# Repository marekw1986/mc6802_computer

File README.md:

# MC6802 computer

Currently this code only consists some I/O routines for MC6802 
based system.

This project is still in development. It's going to be simple BASIC computer.

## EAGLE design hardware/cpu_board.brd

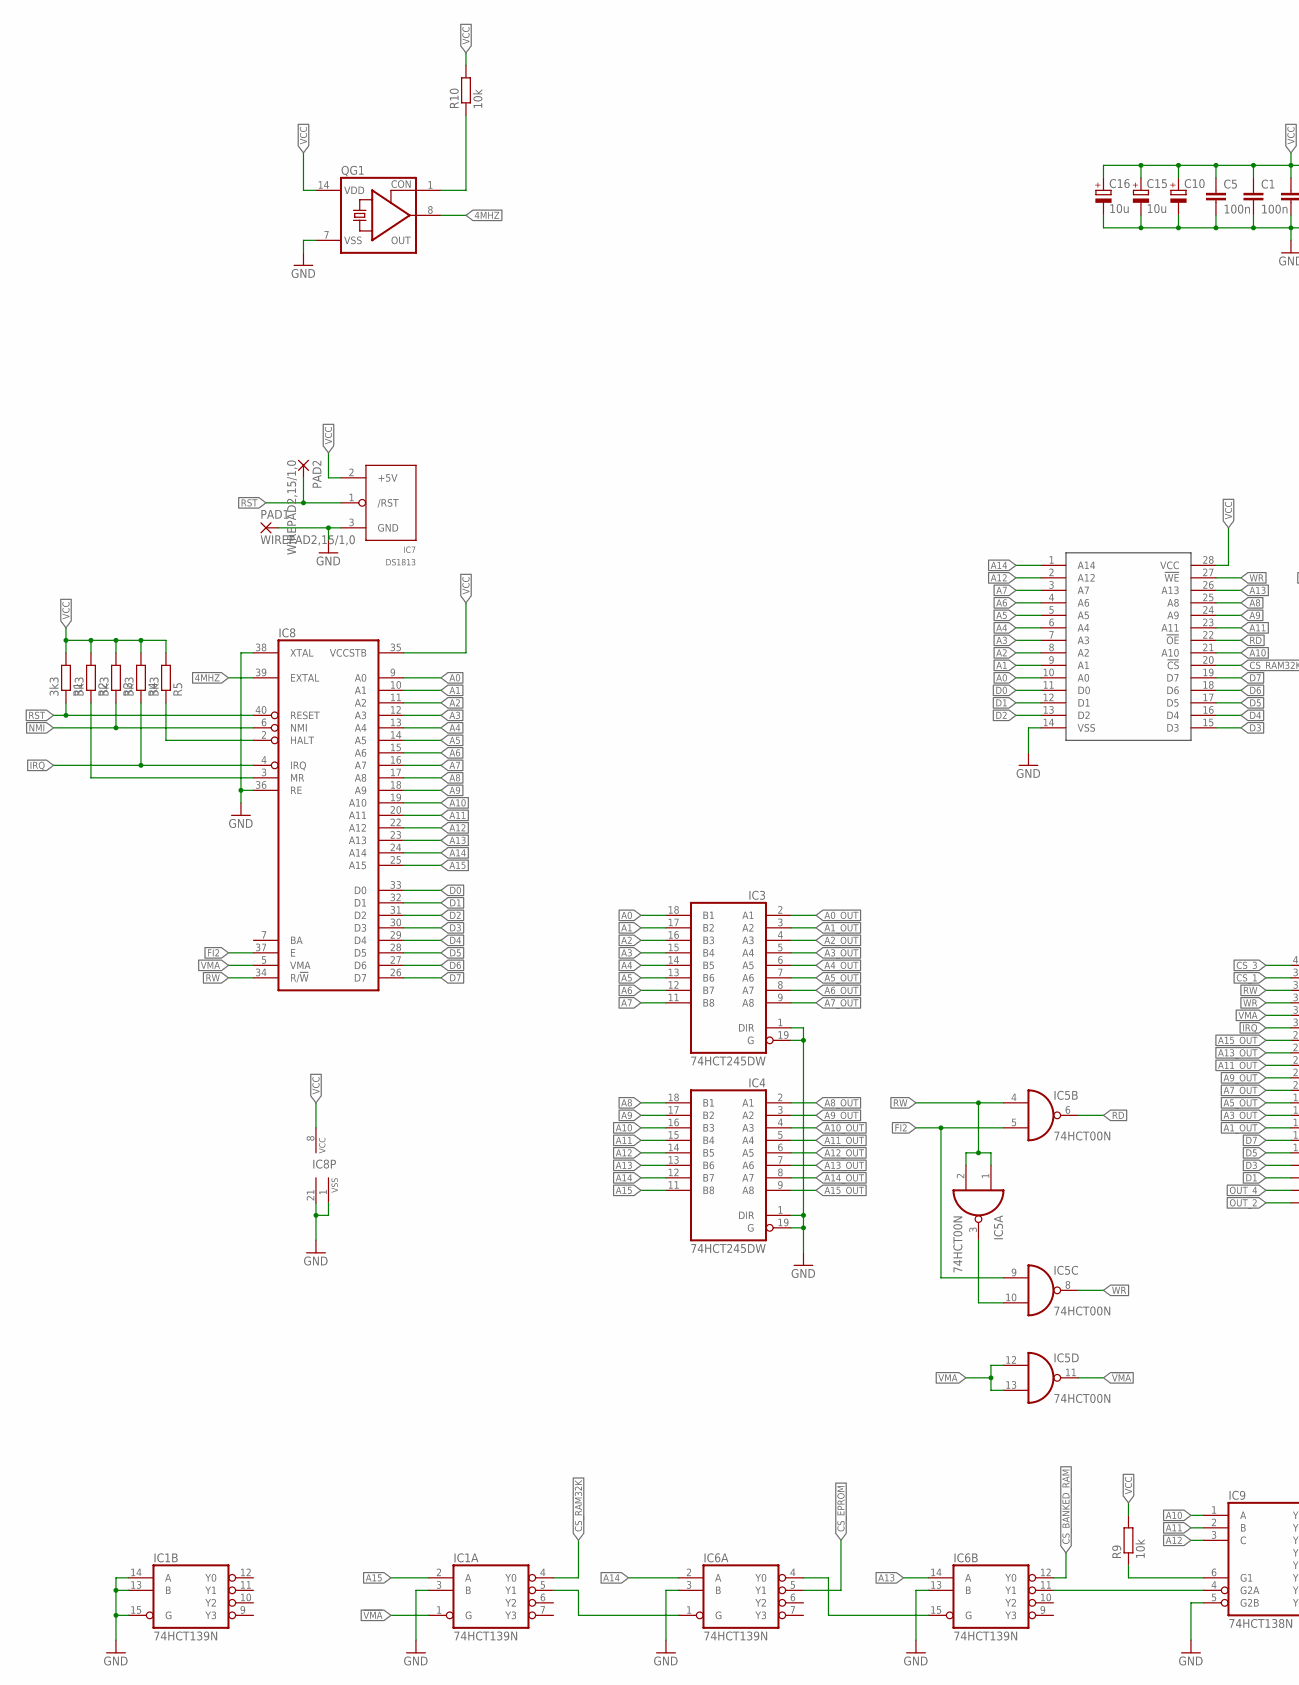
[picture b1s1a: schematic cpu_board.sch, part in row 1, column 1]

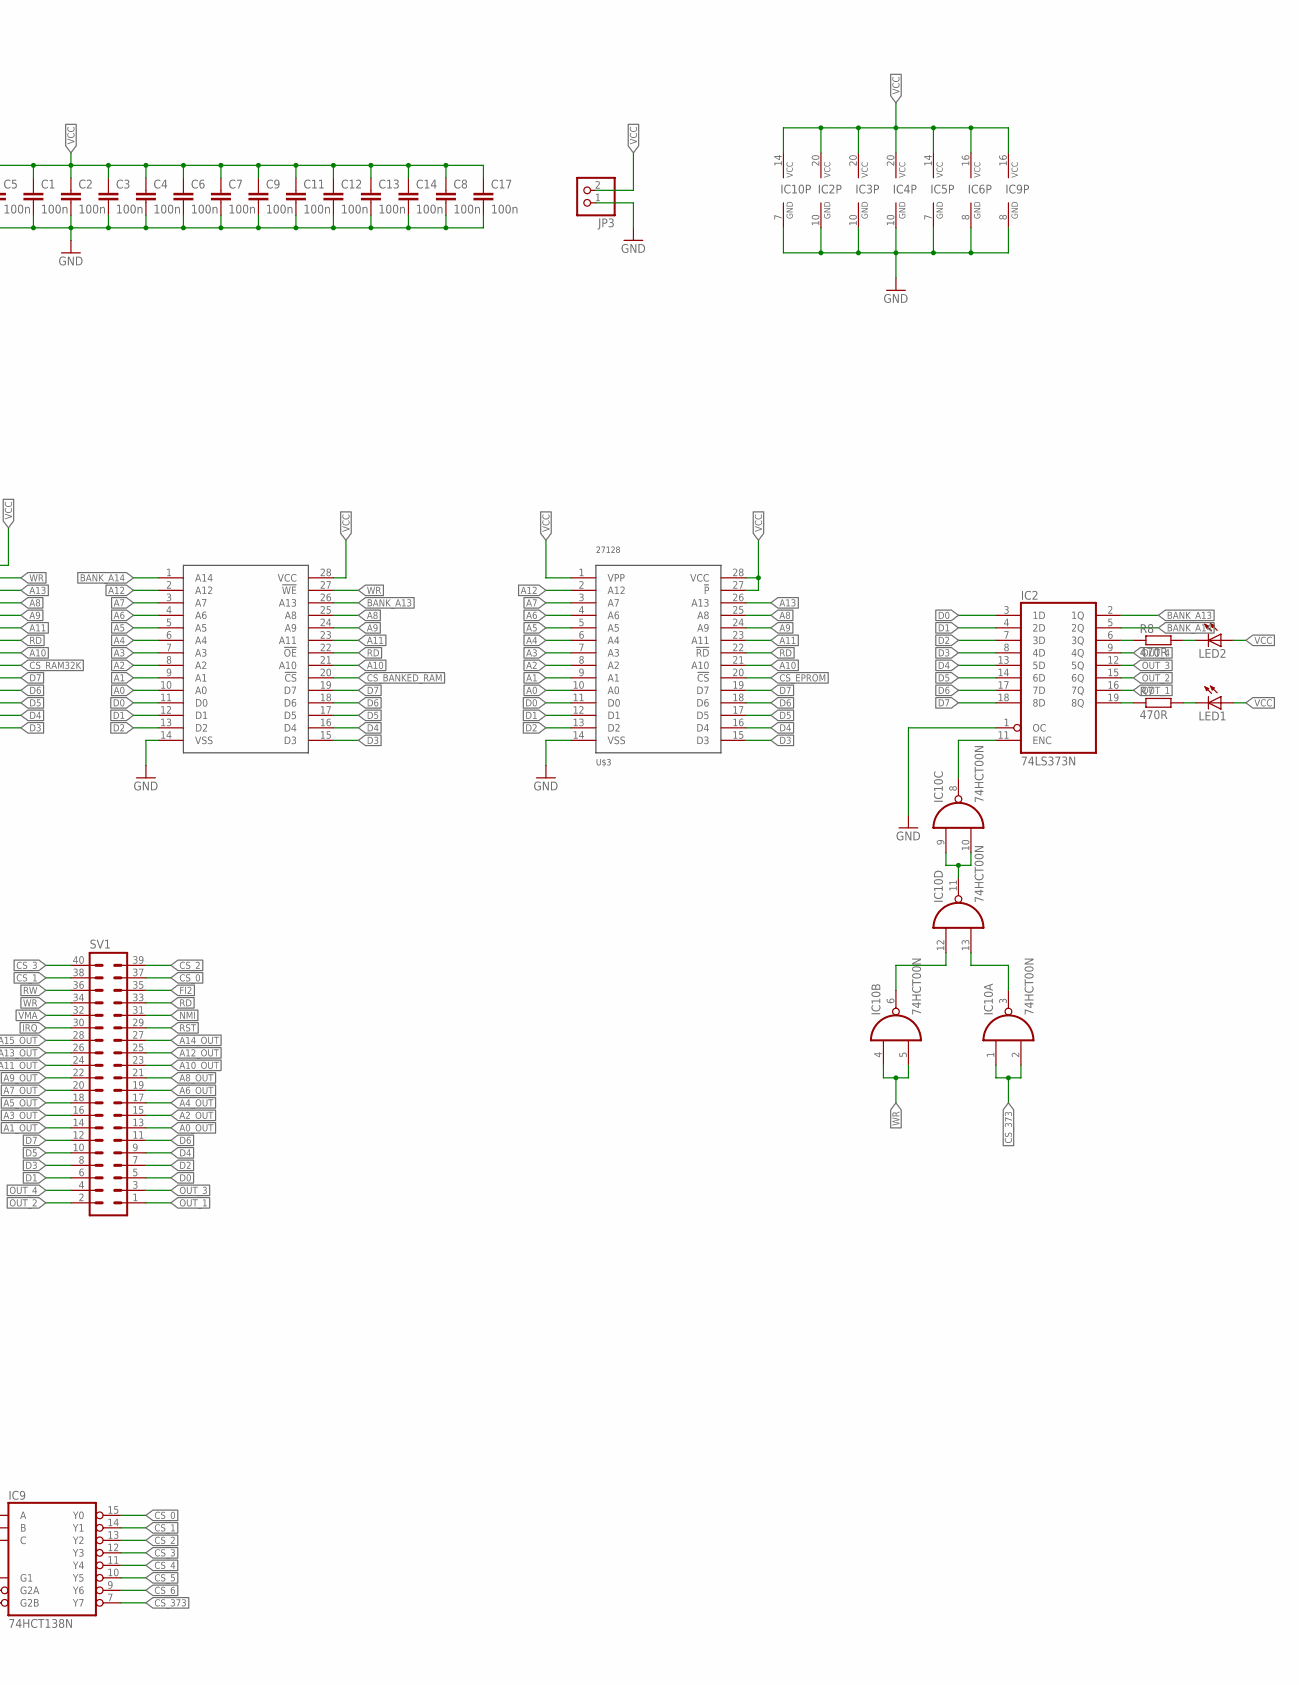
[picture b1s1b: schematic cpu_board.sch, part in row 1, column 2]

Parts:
C1, C2, C3, C4, C6, C8, C9: 100n; C1206
C5, C7, C14: 100n; C0603
C10: CPOL-EUE5-10.5; E5-10,5
C11, C12, C13, C17: 100n; C0805
C15, C16: 10u; SMC_B
IC1, IC6: 74HCT139N; DIL16
IC2: 74LS373N; DIL20
IC3, IC4: 74HCT245DW; SO20W
IC5, IC10: 74HCT00N; DIL14
IC7: DS1813; TO-92
IC8: 6802; DIL40
IC9: 74HCT138N; DIL16
JP3: PINHD-1X2/90; 1X02/90
LED1, LED2: LED5MM
PAD1, PAD2: WIREPAD2,15/1,0; 2,15/1,0
QG1: CRYSTAL_RES-SG51; SG51
R1, R2, R3, R5: 3k3; R1206
R4: 3k3; R0603
R7, R8: 470R; R1206
R9: 10k; 0204/7
R10: 10k; R1206
SV1: ML40L
U$2, U$4: 62256; DIL28-6
U$3: 27128; DIL28

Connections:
4MHZ: IC8.39 (EXTAL), QG1.8 (OUT)
!VMA: IC1.1 (G), IC5.11 (O)
A0: IC3.18 (B1), IC8.9 (A0), U$2.10 (A0), U$3.10 (A0), U$4.10 (A0)
A0_OUT: IC3.2 (A1), SV1.13
A1: IC3.17 (B2), IC8.10 (A1), U$2.9 (A1), U$3.9 (A1), U$4.9 (A1)
A1_OUT: IC3.3 (A2), SV1.14
A2: IC3.16 (B3), IC8.11 (A2), U$2.8 (A2), U$3.8 (A2), U$4.8 (A2)
A2_OUT: IC3.4 (A3), SV1.15
A3: IC3.15 (B4), IC8.12 (A3), U$2.7 (A3), U$3.7 (A3), U$4.7 (A3)
A3_OUT: IC3.5 (A4), SV1.16
A4: IC3.14 (B5), IC8.13 (A4), U$2.6 (A4), U$3.6 (A4), U$4.6 (A4)
A4_OUT: IC3.6 (A5), SV1.17
A5: IC3.13 (B6), IC8.14 (A5), U$2.5 (A5), U$3.5 (A5), U$4.5 (A5)
A5_OUT: IC3.7 (A6), SV1.18
A6: IC3.12 (B7), IC8.15 (A6), U$2.4 (A6), U$3.4 (A6), U$4.4 (A6)
A6_OUT: IC3.8 (A7), SV1.19
A7: IC3.11 (B8), IC8.16 (A7), U$2.3 (A7), U$3.3 (A7), U$4.3 (A7)
A7_OUT: IC3.9 (A8), SV1.20
A8: IC4.18 (B1), IC8.17 (A8), U$2.25 (A8), U$3.25 (A8), U$4.25 (A8)
A8_OUT: IC4.2 (A1), SV1.21
A9: IC4.17 (B2), IC8.18 (A9), U$2.24 (A9), U$3.24 (A9), U$4.24 (A9)
A9_OUT: IC4.3 (A2), SV1.22
A10: IC4.16 (B3), IC8.19 (A10), IC9.1 (A), U$2.21 (A10), U$3.21 (A10), U$4.21 (A10)
A10_OUT: IC4.4 (A3), SV1.23
A11: IC4.15 (B4), IC8.20 (A11), IC9.2 (B), U$2.23 (A11), U$3.23 (A11), U$4.23 (A11)
A11_OUT: IC4.5 (A4), SV1.24
A12: IC4.14 (B5), IC8.22 (A12), IC9.3 (C), U$2.2 (A12), U$3.2 (A12), U$4.2 (A12)
A12_OUT: IC4.6 (A5), SV1.25
A13: IC4.13 (B6), IC6.14 (A), IC8.23 (A13), U$3.26 (A13), U$4.26 (A13)
A13_OUT: IC4.7 (A6), SV1.26
A14: IC4.12 (B7), IC6.2 (A), IC8.24 (A14), U$4.1 (A14)
A14_OUT: IC4.8 (A7), SV1.27
A15: IC1.2 (A), IC4.11 (B8), IC8.25 (A15)
A15_OUT: IC4.9 (A8), SV1.28
BANK_A13: IC2.2 (1Q), U$2.26 (A13)
BANK_A14: IC2.5 (2Q), U$2.1 (A14)
CS_0: IC9.15 (Y0), SV1.37
CS_1: IC9.14 (Y1), SV1.38
CS_2: IC9.13 (Y2), SV1.39
CS_3: IC9.12 (Y3), SV1.40
CS_4: IC9.11 (Y4)
CS_5: IC9.10 (Y5)
CS_6: IC9.9 (Y6)
CS_373: IC9.7 (Y7), IC10.1 (I0), IC10.2 (I1)
CS_BANKED_RAM: IC6.12 (Y0), U$2.20 (!CS)
CS_EPROM: IC6.5 (Y1), U$3.20 (!CS)
CS_RAM32K: IC1.4 (Y0), U$4.20 (!CS)
D0: IC2.3 (1D), IC8.33 (D0), SV1.5, U$2.11 (D0), U$3.11 (D0), U$4.11 (D0)
D1: IC2.4 (2D), IC8.32 (D1), SV1.6, U$2.12 (D1), U$3.12 (D1), U$4.12 (D1)
D2: IC2.7 (3D), IC8.31 (D2), SV1.7, U$2.13 (D2), U$3.13 (D2), U$4.13 (D2)
D3: IC2.8 (4D), IC8.30 (D3), SV1.8, U$2.15 (D3), U$3.15 (D3), U$4.15 (D3)
D4: IC2.13 (5D), IC8.29 (D4), SV1.9, U$2.16 (D4), U$3.16 (D4), U$4.16 (D4)
D5: IC2.14 (6D), IC8.28 (D5), SV1.10, U$2.17 (D5), U$3.17 (D5), U$4.17 (D5)
D6: IC2.17 (7D), IC8.27 (D6), SV1.11, U$2.18 (D6), U$3.18 (D6), U$4.18 (D6)
D7: IC2.18 (8D), IC8.26 (D7), SV1.12, U$2.19 (D7), U$3.19 (D7), U$4.19 (D7)
FI2: IC5.5 (I1), IC5.9 (I0), IC8.37 (E), SV1.35
GND: C1.2, C2.2, C3.2, C4.2, C5.2, C6.2, C7.2, C8.2, C9.2, C10.-, C11.2, C12.2, C13.2, C14.2, C15.-, C16.-, C17.2, IC1.3 (B), IC1.8 (GND), IC1.13 (B), IC1.14 (A), IC1.15 (G), IC2.1 (OC), IC2.10 (GND), IC3.1 (DIR), IC3.10 (GND), IC3.19 (G), IC4.1 (DIR), IC4.10 (GND), IC4.19 (G), IC5.7 (GND), IC6.3 (B), IC6.8 (GND), IC6.13 (B), IC7.3 (GND), IC8.1 (VSS), IC8.21 (VSS), IC8.36 (RE), IC8.38 (XTAL), IC9.5 (G2B), IC9.8 (GND), IC10.7 (GND), JP3.1, PAD1.1, QG1.7 (VSS), U$2.14 (VSS), U$3.14 (VSS), U$4.14 (VSS)
IRQ: IC8.4 (IRQ), R4.1, SV1.30
unnamed: IC1.5 (Y1), IC6.1 (G)
unnamed: IC2.19 (8Q), R7.1
unnamed: LED1.K (C), R7.2
unnamed: IC8.3 (MR), R2.1
unnamed: IC8.2 (HALT), R5.1
unnamed: QG1.1 (CON), R10.1
unnamed: IC2.11 (ENC), IC10.8 (O)
unnamed: IC10.9 (I0), IC10.10 (I1), IC10.11 (O)
unnamed: IC10.3 (O), IC10.13 (I1)
unnamed: IC10.6 (O), IC10.12 (I0)
unnamed: IC2.6 (3Q), R8.1
unnamed: LED2.K (C), R8.2
unnamed: IC5.3 (O), IC5.10 (I1)
unnamed: IC6.4 (Y0), IC6.15 (G)
unnamed: IC9.6 (G1), R9.1
unnamed: IC6.11 (Y1), IC9.4 (G2A)
NMI: IC8.6 (NMI), R3.1, SV1.31
OUT_1: IC2.16 (7Q), SV1.1
OUT_2: IC2.15 (6Q), SV1.2
OUT_3: IC2.12 (5Q), SV1.3
OUT_4: IC2.9 (4Q), SV1.4
RD: IC5.6 (O), SV1.33, U$2.22 (!OE), U$3.22 (!RD), U$4.22 (!OE)
RST: IC7.1 (/RST), IC8.40 (RESET), PAD2.1, R1.1, SV1.29
RW: IC5.1 (I0), IC5.2 (I1), IC5.4 (I0), IC8.34 (R/!W), SV1.36
VCC: C1.1, C2.1, C3.1, C4.1, C5.1, C6.1, C7.1, C8.1, C9.1, C10.+, C11.1, C12.1, C13.1, C14.1, C15.+, C16.+, C17.1, IC1.16 (VCC), IC2.20 (VCC), IC3.20 (VCC), IC4.20 (VCC), IC5.14 (VCC), IC6.16 (VCC), IC7.2 (+5V), IC8.8 (VCC), IC8.35 (VCCSTB), IC9.16 (VCC), IC10.14 (VCC), JP3.2, LED1.A, LED2.A, QG1.14 (VDD), R1.2, R2.2, R3.2, R4.2, R5.2, R9.2, R10.2, U$2.28 (VCC), U$3.1 (VPP), U$3.27 (!P), U$3.28 (VCC), U$4.28 (VCC)
VMA: IC5.12 (I0), IC5.13 (I1), IC8.5 (VMA), SV1.32
WR: IC5.8 (O), IC10.4 (I0), IC10.5 (I1), SV1.34, U$2.27 (!WE), U$4.27 (!WE)

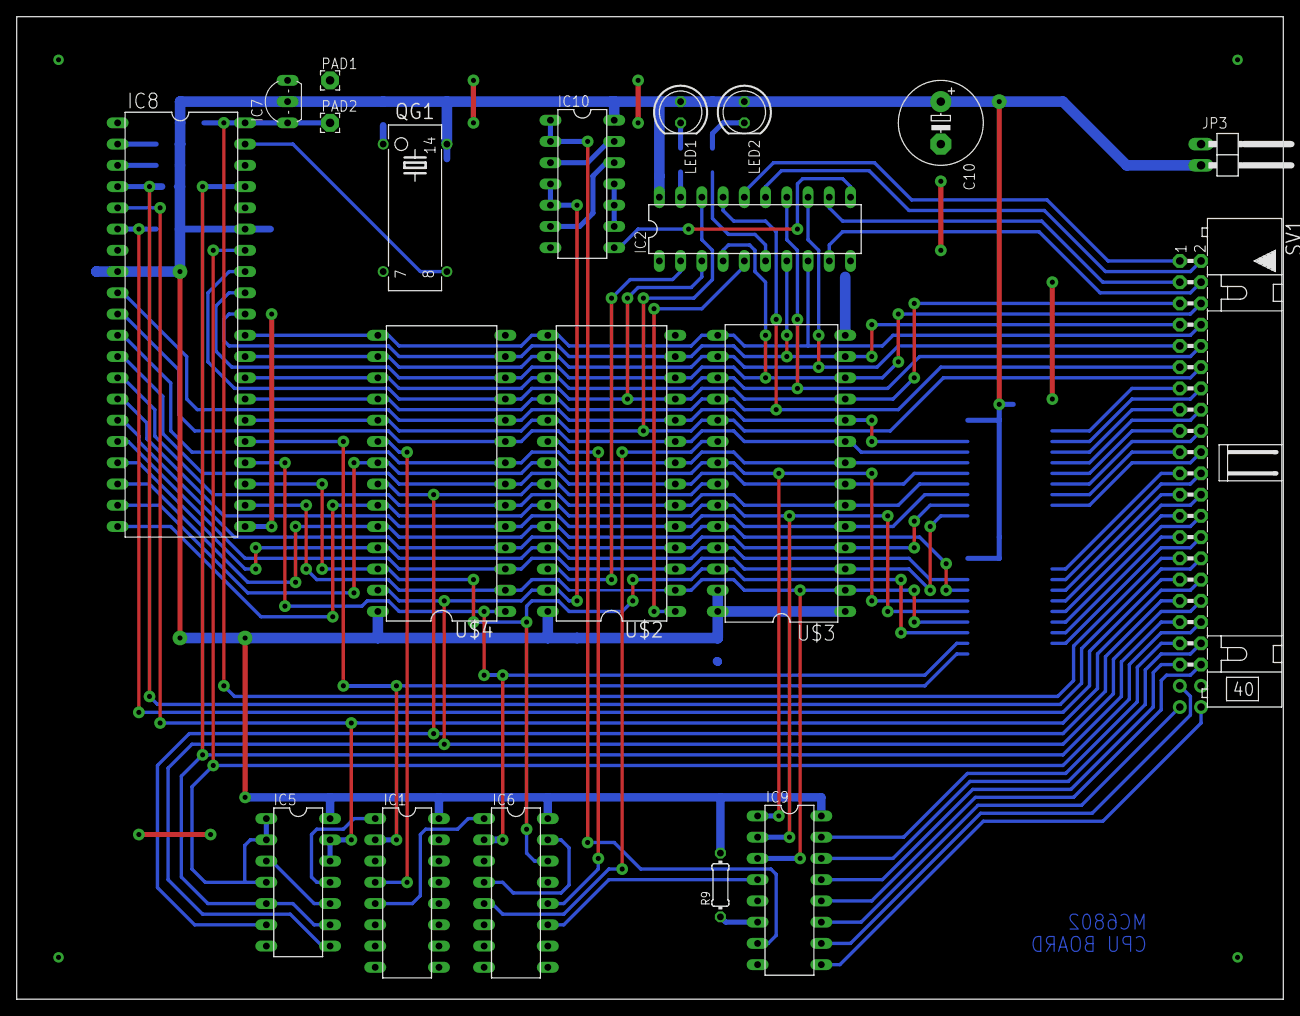
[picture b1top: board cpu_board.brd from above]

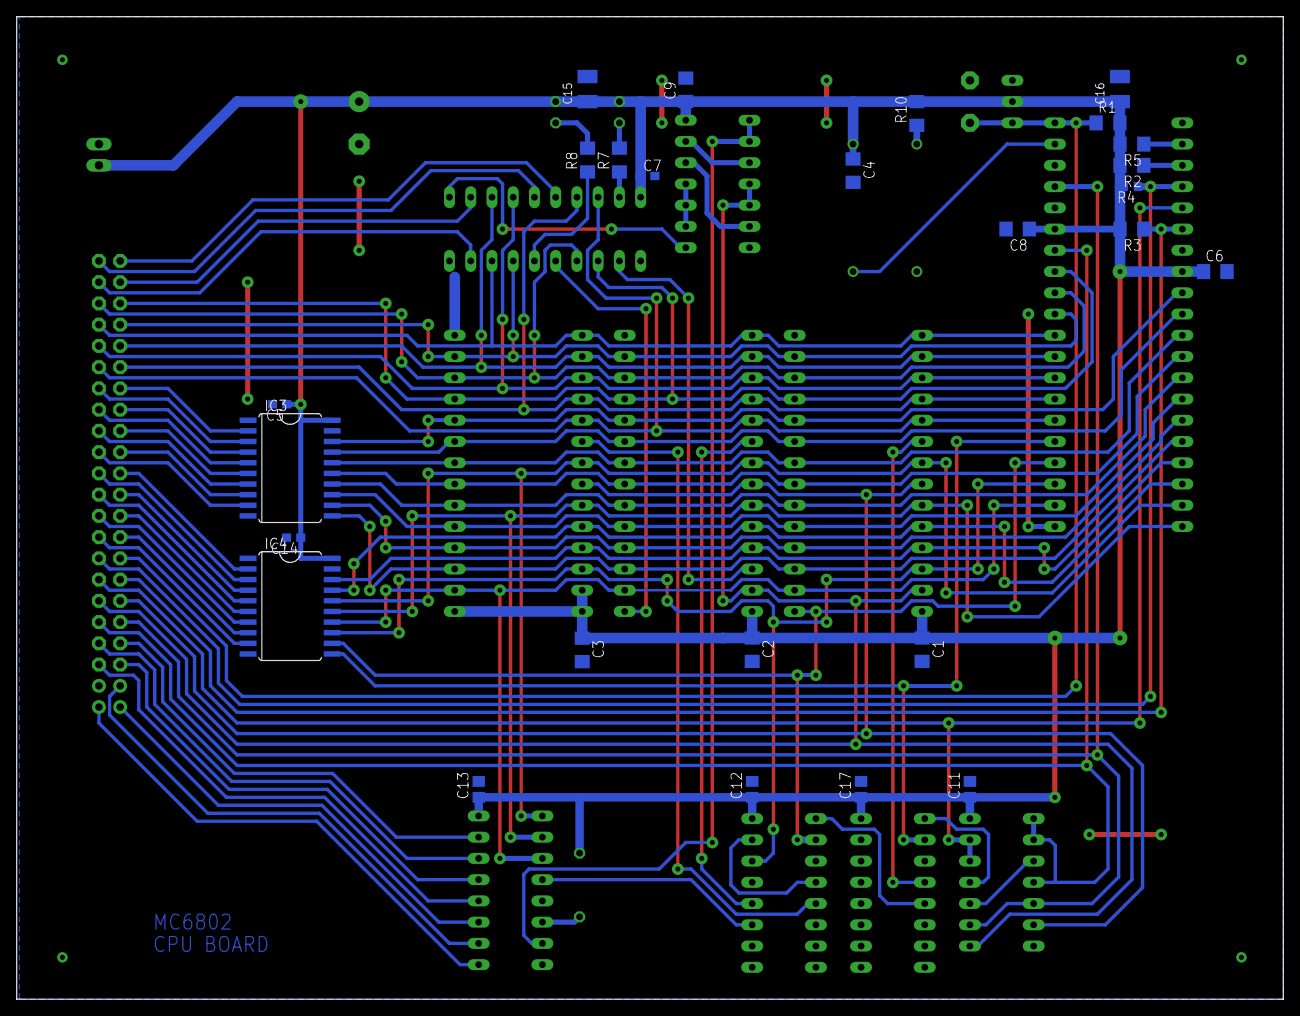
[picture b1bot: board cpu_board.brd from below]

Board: 2 copper layers, 151.4 x 117.5 mm, 46 parts (26 on the bottom side), 82 nets.

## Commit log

2020-08-27 README.md updated
2020-09-18 PCB added
2021-03-12 gitignore
